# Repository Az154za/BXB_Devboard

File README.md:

# BXB_Devboard
Well this is a custom devboard a guided project from hackclub

# Schematic
This is an overview of the schematic

# PCB

# 3D overview

## Bill of Materials (BOM)

| Component | Price | Link |
|-----------|-------|------|
| PCB | $54.60 | [JLCPCB](https://jlcpcb.com) |
| DHT11 | $1.12 | [AliExpress](https://fr.aliexpress.com/item/1005008953430940.html) |
| **Total** | **$55.72** | |

I hope you like the project don't forget to comment on this project

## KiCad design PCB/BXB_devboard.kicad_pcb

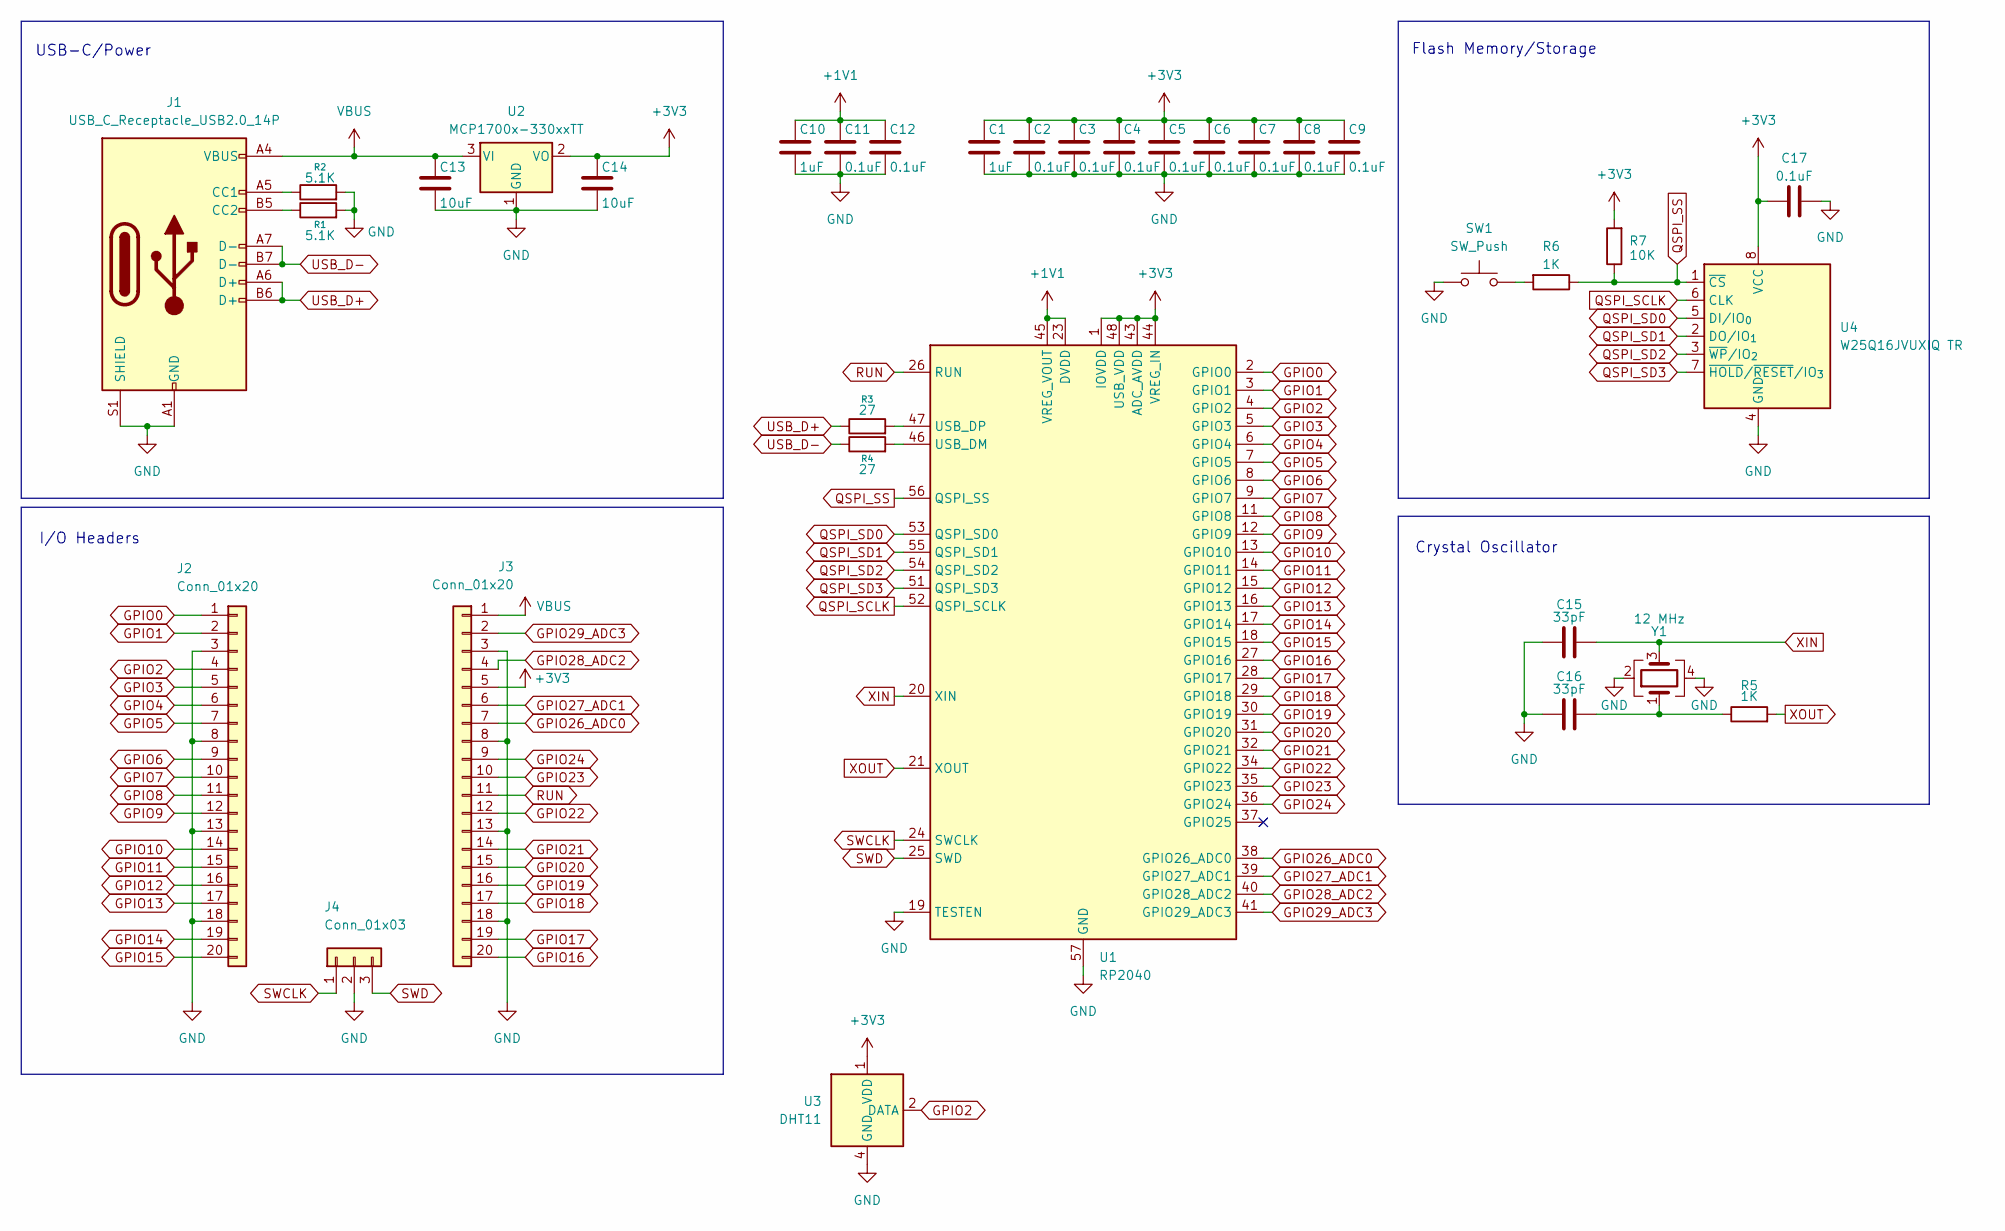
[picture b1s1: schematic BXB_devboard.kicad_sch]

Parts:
C1, C10: 1uF; C_0402_1005Metric
C2, C3, C4, C5, C6, C7, C8, C9, C11, C12, C17: 0.1uF; C_0402_1005Metric
C13, C14: 10uF; C_0603_1608Metric
C15, C16: 33pF; C_0402_1005Metric
J1: USB_C_Receptacle_USB2.0_14P; USB_C_Receptacle_HRO_TYPE-C-31-M-12
J2, J3: Conn_01x20; PinHeader_1x20_P2.54mm_Vertical
J4: Conn_01x03; PinHeader_1x03_P2.54mm_Vertical
R1, R2: 5.1K; R_0402_1005Metric
R3, R4: 27; R_0402_1005Metric
R5, R6: 1K; R_0402_1005Metric
R7: 10K; R_0402_1005Metric
SW1: SW_Push; SW_Push_SPST_NO_Alps_SKRK
U1: RP2040; QFN-56-1EP_7x7mm_P0.4mm_EP3.2x3.2mm
U2: MCP1700x-330xxTT; SOT-23
U3: DHT11; Aosong_DHT11_5.5x12.0_P2.54mm
U4: W25Q16JVUXIQ TR; Winbond_USON-8-1EP_3x2mm_P0.5mm_EP0.2x1.6mm
Y1: 12 MHz; Crystal_SMD_3225-4Pin_3.2x2.5mm

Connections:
+1V1: C10.1, C11.1, C12.1, U1.23 (DVDD), U1.45 (VREG_VOUT), U1.50 (DVDD)
+3V3: C1.1, C2.1, C3.1, C4.1, C5.1, C6.1, C7.1, C8.1, C9.1, C14.1, C17.1, J3.5, R7.2, U1.1 (IOVDD), U1.10 (IOVDD), U1.22 (IOVDD), U1.33 (IOVDD), U1.42 (IOVDD), U1.43 (ADC_AVDD), U1.44 (VREG_IN), U1.48 (USB_VDD), U1.49 (IOVDD), U2.2 (VO), U3.1 (VDD), U4.8 (VCC)
GND: C1.2, C2.2, C3.2, C4.2, C5.2, C6.2, C7.2, C8.2, C9.2, C10.2, C11.2, C12.2, C13.2, C14.2, C15.1, C16.1, C17.2, J1.A1 (GND), J1.A12 (GND), J1.B1 (GND), J1.B12 (GND), J1.S1 (SHIELD), J2.3, J2.8, J2.13, J2.18, J3.3, J3.8, J3.13, J3.18, J4.2, R1.2, R2.2, SW1.1, U1.19 (TESTEN), U1.57 (GND), U2.1 (GND), U3.4 (GND), U4.4 (GND), Y1.2, Y1.4
GPIO0: J2.1, U1.2 (GPIO0)
GPIO1: J2.2, U1.3 (GPIO1)
GPIO2: J2.4, U1.4 (GPIO2), U3.2 (DATA)
GPIO3: J2.5, U1.5 (GPIO3)
GPIO4: J2.6, U1.6 (GPIO4)
GPIO5: J2.7, U1.7 (GPIO5)
GPIO6: J2.9, U1.8 (GPIO6)
GPIO7: J2.10, U1.9 (GPIO7)
GPIO8: J2.11, U1.11 (GPIO8)
GPIO9: J2.12, U1.12 (GPIO9)
GPIO10: J2.14, U1.13 (GPIO10)
GPIO11: J2.15, U1.14 (GPIO11)
GPIO12: J2.16, U1.15 (GPIO12)
GPIO13: J2.17, U1.16 (GPIO13)
GPIO14: J2.19, U1.17 (GPIO14)
GPIO15: J2.20, U1.18 (GPIO15)
GPIO16: J3.20, U1.27 (GPIO16)
GPIO17: J3.19, U1.28 (GPIO17)
GPIO18: J3.17, U1.29 (GPIO18)
GPIO19: J3.16, U1.30 (GPIO19)
GPIO20: J3.15, U1.31 (GPIO20)
GPIO21: J3.14, U1.32 (GPIO21)
GPIO22: J3.12, U1.34 (GPIO22)
GPIO23: J3.10, U1.35 (GPIO23)
GPIO24: J3.9, U1.36 (GPIO24)
GPIO26_ADC0: J3.7, U1.38 (GPIO26_ADC0)
GPIO27_ADC1: J3.6, U1.39 (GPIO27_ADC1)
GPIO28_ADC2: J3.4, U1.40 (GPIO28_ADC2)
GPIO29_ADC3: J3.2, U1.41 (GPIO29_ADC3)
unnamed: C16.2, R5.1, Y1.1
unnamed: J1.A5 (CC1), R2.1
unnamed: J1.B5 (CC2), R1.1
unnamed: R6.2, SW1.2
unnamed: R4.2, U1.46 (USB_DM)
unnamed: R3.2, U1.47 (USB_DP)
QSPI_SCLK: U1.52 (QSPI_SCLK), U4.6 (CLK)
QSPI_SD0: U1.53 (QSPI_SD0), U4.5 (DI/IO_{0})
QSPI_SD1: U1.55 (QSPI_SD1), U4.2 (DO/IO_{1})
QSPI_SD2: U1.54 (QSPI_SD2), U4.3 (~WP/IO_{2})
QSPI_SD3: U1.51 (QSPI_SD3), U4.7 (~HOLD/~RESET/IO_{3})
QSPI_SS: R6.1, R7.1, U1.56 (QSPI_SS), U4.1 (~CS)
RUN: J3.11, U1.26 (RUN)
SWCLK: J4.1, U1.24 (SWCLK)
SWD: J4.3, U1.25 (SWD)
USB_D+: J1.A6 (D+), J1.B6 (D+), R3.1
USB_D-: J1.A7 (D-), J1.B7 (D-), R4.1
VBUS: C13.1, J1.A4 (VBUS), J1.A9 (VBUS), J1.B4 (VBUS), J1.B9 (VBUS), J3.1, U2.3 (VI)
XIN: C15.2, U1.20 (XIN), Y1.3
XOUT: R5.2, U1.21 (XOUT)

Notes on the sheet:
Flash Memory/Storage
I/O Headers
Crystal Oscillator
USB-C/Power

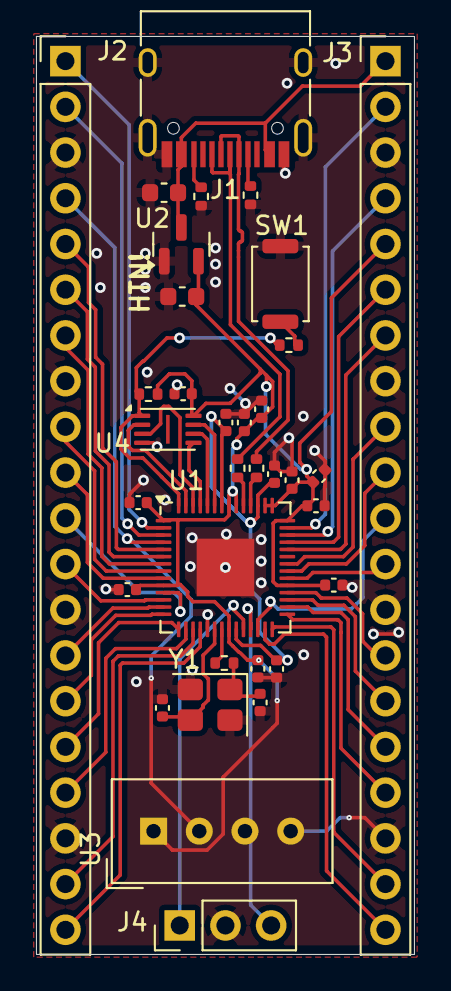
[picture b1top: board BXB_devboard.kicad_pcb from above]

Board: 2 copper layers, 21.0 x 51.0 mm, 34 parts (0 on the bottom side), 52 nets.

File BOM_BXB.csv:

JLCPCB BOM Tool - BOM Matching,,,,,,,,,,,,,,,,,;
"BOM name：BOM-JLCPCB Assembly Order.xlsx,,,Download Time：2025-10-01 10:21:17,,,,""* Our matching results are updated in real-time, but stock and prices may change. ";
"If it's been over 24 hours, please re-match before placing your order."",,,,,,,,,,";
PCB Assembled Qty：5,,,Est. Total Price：11.5620,,,,,,,,,,,,,,;
Your BOM,,,,,Matched Parts,,,,,,,Order Information,,,,,;
Top Designator,Bottom Designator,Comment,Footprint,JLCPCB Part #,Matches,Part # ,Manufacturer,Footprint,Description,Category,Warning,JLCPCB Part #,Product link,Lib Type,Qty,Source,Total Price ($);
C1,C10,,1uF,C_0402_1005Metric,,Select by Customer,CL05A105KA5NQNC,Samsung Electro-Mechanics,0402,1uF 25V X5R ±10% 0402 Multilayer Ceramic Capacitors MLCC - SMD/SMT ROHS,Multilayer Ceramic Capacitors MLCC - SMD/SMT,,C52923,https://jlcpcb.com/partdetail/53938-CL05A105KA5NQNC/C52923,Basic,10,10 JLCPCB,0.029;
C8,C6,C5,C4,C2,C7,C11,C9,C12,C17,C3,,0.1uF,C_0402_1005Metric,,Select by Customer,CL05B104KO5NNNC,Samsung Electro-Mechanics,0402,100nF 16V X7R ±10% 0402 Multilayer Ceramic Capacitors MLCC - SMD/SMT ROHS,Multilayer Ceramic Capacitors MLCC - SMD/SMT,1.The comment (CL05B104KO5NNNC) of this part does not match the one (0.1uF) provided in your BOM. Please confirm;,C1525,https://jlcpcb.com/partdetail/1877-CL05B104KO5NNNC/C1525,Basic,55,55 JLCPCB,0.0605
C13,C14,,10uF,C_0603_1608Metric,,Select by System,CL10A106KP8NNNC,Samsung Electro-Mechanics,0603,10V 10uF X5R ±10% 0603 Multilayer Ceramic Capacitors MLCC - SMD/SMT ROHS,Multilayer Ceramic Capacitors MLCC - SMD/SMT,,C19702,https://jlcpcb.com/partdetail/20411-CL10A106KP8NNNC/C19702,Basic,10,10 JLCPCB,0.056;
C16,C15,,33pF,C_0402_1005Metric,,Select by Customer,0402CG330J500NT,FH (Guangdong Fenghua Advanced Tech),0402,33pF 50V C0G ±5% 0402 Multilayer Ceramic Capacitors MLCC - SMD/SMT ROHS,Multilayer Ceramic Capacitors MLCC - SMD/SMT,,C1562,https://jlcpcb.com/partdetail/1914-0402CG330J500NT/C1562,Basic,10,10 JLCPCB,0.01;
J1,,USB_C_Receptacle_USB2.0_14P,USB_C_Receptacle_HRO_TYPE-C-31-M-12,,Select by Customer,TYPE-C-31-M-12,Korean Hroparts Elec,SMD,1 16P 5A Female Type-C SMD USB Connectors ROHS,USB Connectors,,C165948,https://jlcpcb.com/partdetail/Korean_HropartsElec-TYPE_C_31_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,Extended,5,5 JLCPCB,0.8445;
"J3,J2,,Conn_01x20,PinHeader_1x20_P2.54mm_Vertical,,Select by Customer,2.54-1*20P直针,BOOMELE(Boom Precision Elec),""插件,P=2.54mm"",""-40℃~+105℃ 1 1x20P 2.54mm 20P 3A Black Brass Pin Header Through Hole Plugin,P=2.54mm Pin Headers ROHS"",Pin Headers,,C50981,https://jlcpcb.com/partdetail/51993-2_54_1_20P/C50981,Extended,0,0 JLCPCB,0";
"J4,,Conn_01x03,PinHeader_1x03_P2.54mm_Vertical,,Select by Customer,1.27-1*3P针,BOOMELE(Boom Precision Elec),""插件,P=1.27mm"",""-55℃~+105℃ 1 1.27mm 1mm 1x3P 2.3mm 3A 3P 3mm Black Brass Pin Header Through Hole Plugin,P=1.27mm Pin Headers ROHS"",Pin Headers,,C24980,https://jlcpcb.com/partdetail/25717-1_27_1_3P/C24980,Extended,0,0 JLCPCB,0";
R2,R1,,5.1K,R_0402_1005Metric,,Select by Customer,0402WGF5101TCE,UNI-ROYAL(Uniroyal Elec),0402,-55℃~+155℃ 5.1kΩ 50V 62.5mW Thick Film Resistor ±1% ±100ppm/℃ 0402 Chip Resistor - Surface Mount ROHS,Chip Resistor - Surface Mount,,C25905,https://jlcpcb.com/partdetail/26648-0402WGF5101TCE/C25905,Basic,10,10 JLCPCB,0.005;
R3,R4,,27,R_0402_1005Metric,,Select by Customer,0402WGF270JTCE,UNI-ROYAL(Uniroyal Elec),0402,-55℃~+155℃ 27Ω 50V 62.5mW Thick Film Resistor ±1% ±100ppm/℃ 0402 Chip Resistor - Surface Mount ROHS,Chip Resistor - Surface Mount,1.The comment (0402WGF270JTCE) of this part does not match the one (27) provided in your BOM. Please confirm;,C25100,https://jlcpcb.com/partdetail/25843-0402WGF270JTCE/C25100,Extended,22,22 JLCPCB,0.011
R6,R5,,1K,R_0402_1005Metric,,Select by Customer,0402WGF1001TCE,UNI-ROYAL(Uniroyal Elec),0402,-55℃~+155℃ 1kΩ 50V 62.5mW Thick Film Resistor ±1% ±100ppm/℃ 0402 Chip Resistor - Surface Mount ROHS,Chip Resistor - Surface Mount,1.The comment (0402WGF1001TCE) of this part does not match the one (1K) provided in your BOM. Please confirm;,C11702,https://jlcpcb.com/partdetail/12256-0402WGF1001TCE/C11702,Basic,10,10 JLCPCB,0.005
R7,,10K,R_0402_1005Metric,,Select by Customer,0402WGF1002TCE,UNI-ROYAL(Uniroyal Elec),0402,-55℃~+155℃ 10kΩ 50V 62.5mW Thick Film Resistor ±1% ±100ppm/℃ 0402 Chip Resistor - Surface Mount ROHS,Chip Resistor - Surface Mount,1.The comment (0402WGF1002TCE) of this part does not match the one (10K) provided in your BOM. Please confirm;,C25744,https://jlcpcb.com/partdetail/26487-0402WGF1002TCE/C25744,Basic,5,5 JLCPCB,0.0025
"SW1,,SW_Push,SW_Push_SPST_NO_Alps_SKRK,,Select by Customer,TS-1088-AR02016,XUNPU,""SMD,4x3mm"",""-30℃~+80℃ 1.6N 100,000 Cycles 12V 2mm 3mm 4mm 50mA Black Round Button SMD(SMT) Tab SPST Surface Mount,Vertical Without Bracket SMD,4x3mm Tactile Switches ROHS"",Tactile Switches,,C720477,https://jlcpcb.com/partdetail/XUNPU-TS_1088AR02016/C720477,Basic,5,5 JLCPCB,0.2115";
U1,,RP2040,QFN-56-1EP_7x7mm_P0.4mm_EP3.2x3.2mm,,Select by Customer,RP2040,Raspberry Pi,LQFN-56(7x7),12bit 133MHz 30 LQFN-56(7x7) Microcontrollers (MCU/MPU/SOC) ROHS,Microcontrollers (MCU/MPU/SOC),,C2040,https://jlcpcb.com/partdetail/RaspberryPi-RP2040/C2040,Extended,5,5 JLCPCB,5.5275;
"U2,,MCP1700x-330xxTT,SOT-23,,Select by Customer,MCP1700T-3302E/TT,Microchip Tech,SOT-23,""-40℃~+125℃@(Tj) 1 1.6uA 178mV@(250mA) 250mA 3.3V 44dB@(100Hz) 6V Fixed Over Temperature Protection Positive SOT-23 Voltage Regulators - Linear, Low Drop Out (LDO) Regulators ROHS"",""Voltage Regulators - Linear, Low Drop Out (LDO) Regulators"",,C39051,https://jlcpcb.com/partdetail/MicrochipTech-MCP1700T_3302ETT/C39051,Extended,5,5 JLCPCB,1.717";
"U4,,W25Q16JVUXIQTR,Winbond_USON-8-1EP_3x2mm_P0.5mm_EP0.2x1.6mm,,Select by Customer,W25Q16JVUXIQ,Winbond Elec,USON-8-EP(2x3),""100,000 Cycles 133MHz 16Mbit 2.7V~3.6V 20 Years 3ms SPI USON-8-EP(2x3) NOR FLASH ROHS"",NOR FLASH,1.The comment (W25Q16JVUXIQ) of this part does not match the one (W25Q16JVUXIQTR) provided in your BOM. Please confirm";,C2843335,https://jlcpcb.com/partdetail/WinbondElec-W25Q16JVUXIQ/C2843335,Extended,5,5 JLCPCB,2.76
Y1,,12MHz,Crystal_SMD_3225-4Pin_3.2x2.5mm,,Select by Customer,X322512MSB4SI,YXC Crystal Oscillators,SMD3225-4P,-40℃~+85℃ 12MHz 20pF Crystal Oscillator ±10ppm ±20ppm SMD3225-4P Crystals ROHS,Crystals,,C9002,https://jlcpcb.com/partdetail/YXC_CrystalOscillators-X322512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,Basic,5,5 JLCPCB,0.3225;
U3,,DHT11,Sensor:Aosong_DHT11_5.5x12.0_P2.54mm;

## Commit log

2026-01-03 Update README with project details and images
    Added project description, schematic, PCB, and 3D overview images.
2026-01-14 Update BOM_JLCPCB with new matching results
2026-01-26 Modify BOM_JLCPCB.csv with new and corrected parts
    Updated BOM_JLCPCB.csv with new entries and corrected parts.
2026-01-26 Update BOM_JLCPCB.csv with new entries and corrections
2026-02-16 Fix DHT11 link in BOM section
    Updated DHT11 link in BOM section for clarity.
2026-02-16 Update BOM section to use markdown table format
    Formatted the Bill of Materials section into a table.
2026-02-16 Update PCB price and total in README
